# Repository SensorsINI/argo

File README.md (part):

# Argo Autonomous Sailboat

An autonomous sailboat system based on Dragonforce 65 hull, running on Orange Pi Zero 2W with ROS2. The system includes comprehensive sensor integration, autonomous navigation, and safety monitoring.

[argo freecad 3d.webm](https://github.com/user-attachments/assets/29d93eb4-6dfb-44b6-a583-b5699d12e7a1)

## News
- **May 2026:** After ignominious series of problems at CCNW with cabling, water leaks, GPS and many other issues and only 30m of actual seawater sailing, came back to INI to fix these problems. Now IMU is working, GPS is working, dashboard has map display, there are new cable glands and a new hull that has been air-pressure tested for leaks. We are ready now for water trials again.
- **Mar 2026:** Version 4 of argo PCB with bug fixes, wind sensor on separate I2C bus, and new buzzer. Version 3 of the wind sensor PCB with RGBW LED controller. See [Argo2: Robot Sailboat](https://docs.google.com/presentation/d/15X9GgjOmHowyNMNPRnduzyOgwyVcawP_Lhy54-Hc9cc/edit?usp=sharing) slides presented online at [Embodied Intelligence Conference](https://ei26.embodied-intelligence.org/) 20 March 2026.
- **Feb 2026:** Updated [wind sensor design PCB and housing](pcb/WindSensor/WindSensor-rev1/) complete. 3D parts for wind sensor I2C cable and mast step up completed and printed.
- **Jan 2026:** [Argo main PCB version 3](pcb/argo-v9-stable/argo-v9-stable-rev3/) completed and seems fully functional with no surgery needed.
- **Aug-Dec 2025:** Intense development of new [Argo PCB](pcb/) and [ROS2 software framework](nodes/). System services developed (see [`power_control/argo_power_control.py`](power_control/argo_power_control.py) and [`launch/argo_lifecycle_manager.py`](launch/argo_lifecycle_manager.py)) along with robust [lifecycle management](launch/argo_lifecycle_manager.py) and [battery/power control](power_control/argo_power_control.py).
- **Oct-Nov 2025:** Developed first version of [Argo simulator](simulator/).  
  - See [simulator/sailboat-playground/README.md](simulator/sailboat-playground/README.md) for usage and architecture.  
  - Additional docs: [Simulation Guide](docs/SIMULATION.md), [Debug Simulation Guide](docs/README-debug-simulation.md)  

## Installation

Pick **Argo (boat)** or **Host (PC)** below. ROS 2 **must match your Ubuntu LTS**: 22.04 (Jammy) → **Humble**; 24.04 (Noble) → **Jazzy**. Use the official [ROS 2 Ubuntu (deb) install](https://docs.ros.org/en/jazzy/Installation/Ubuntu-Install-Debs.html) page that corresponds to your ROS release.

### Argo (boat — Orange Pi Zero 2W)

On the robot, the stack targets **Ubuntu 22.04–based** Armbian and **ROS 2 Humble**. Bring up I²C/UART/PWM overlays, the radio/servo kernel module, Python dependencies, systemd services, and power control as described in the [launch](launch/) tree.

```bash
cd ~/argo   # or your clone path
sudo apt update && sudo apt upgrade -y
# Install ROS 2 Humble (.deb), then in each shell you use for builds:
#   source /opt/ros/humble/setup.bash

make install-all          # Python deps + optional hardware (see Makefile / messages)
make install-argo-cli
source ~/.bashrc
make -C launch install    # install systemd units; enable per docs
```

#### First-time SD card and hardware bring-up

**1. Flash Orange Pi OS** using Orange Pi Imager or equivalent.

**2. Initial system setup**

```bash
sudo apt update && sudo apt upgrade -y
sudo apt install python3-pip python3-dev build-essential
sudo apt install i2c-tools device-tree-compiler git
sudo apt install ros-humble-desktop
```

**3. Clone repository**

```bash
cd /home/orangepi
git clone https://github.com/SensorsINI/argo.git
cd argo
```

**4. Python and ROS helpers**

```bash
make install-python-deps   # requirements.txt on the boat
# If needed:
sudo apt install python3-rclpy python3-std-msgs python3-geometry-msgs
```

**5. Hardware configuration**

Edit `/boot/orangepiEnv.txt` and add overlays:

```
overlays=pi-i2c0 disable-uart0 ph-uart5 pi-pwm2 pi-pwm4
user_overlays=argo_radio_servo_overlay
```

Build and load the PWM capture module:

```bash
cd ~/argo/nodes/pwm_capture_module
make all
sudo modprobe argo_radio_servo_module   # or reboot
```

Add your user to hardware groups:

```bash
sudo usermod -a -G i2c,dialout $USER
# log out and back in
```

**6. Verify**

```bash
sudo i2cdetect -y 0
lsmod | grep argo
ls -la /sys/kernel/argo_radio_servo/
sudo cat /dev/ttyS5
```

**7. CLI and services**

```bash
make install-argo-cli && source ~/.bashrc
make -C launch install
sudo systemctl daemon-reload
sudo systemctl enable argo_launch.service
```

### Host (simulation, Foxglove, remote monitoring)

Use this on a **laptop or workstation** for **local simulation** (`asim`), **Foxglove Studio** (same Wi‑Fi, VPN, or SSH tunnel), log playback, and shore-side scripts. The boat still runs ROS 2 on the Orange Pi; your host subscribes/records like any ROS 2 client. **LoRa** is a boat link—the monitoring machine uses normal network ROS 2 or recorded bags unless you run a separate LoRa gateway stack.

**Prerequisites:** Ubuntu **22.04** or **24.04** (see mapping to Humble/Jazzy above), `git`, `make`, `sudo`, and network access for `apt`.

**One-shot bootstrap (Ubuntu 22.04 or 24.04):**

```bash
cd /path/to/argo
make host-setup
source ~/.bashrc                     # reload Argo dotfiles in this terminal (or open a new tab)
# Dotfiles auto-source the first ROS found under /opt/ros (jazzy, iron, humble, rolling) when ROS_DISTRO is unset.

source .venv/bin/activate            # optional; pip tooling (argcomplete, pyglet, …)
asim
```

If a command in **this** terminal cannot find `rclpy` or `ros2` right after `host-setup`, the ROS underlay is not loaded yet: run `source ~/.bashrc` (as above), or explicitly `source /opt/ros/humble/setup.bash` / `source /opt/ros/jazzy/setup.bash` matching your install.

`make host-setup` **refuses to run on Orange Pi** (use `make install-all` on the boat). It:

- Adds **`/etc/apt/sources.list.d/ros2-latest.list`** only if no file already references **packages.ros.org/ros2/ubuntu** (avoids a second `Signed-By` if you installed ROS 2 from the official doc first)  
- Installs **`ros-<distro>-ros-base`** when `/opt/ros/<distro>` is absent (Jammy → `humble`, Noble → `jazzy`, or override with `ROS_DISTRO=`)  
- Runs **`make install-deps`** (single `apt-get update`, then Argo’s ROS .deb set, Foxglove bridge, MCAP storage)  
- Runs **`make setup-venv`** (creates `.venv` with **uv** if available, otherwise `python3 -m venv`, and installs **`requirements-host.txt`**) then **`make install-python-deps`** (same host requirements file again into `.venv`—idempotent on a PC)  
- Runs **`make install-argo-cli`** and **`make submodule-init`** (`install-argo-cli` appends **`source <repo>/dotfiles/bashrc`** to **`~/.bashrc`**; that file auto-sources **`/opt/ros/<distro>/setup.bash`** when **`ROS_DISTRO`** is not already set)  

**Tab completion (optional):** Global argcomplete is **not** installed automatically on every shell (keeps login fast). After `host-setup`, run once: `activate-global-python-argcomplete3 --user` or `activate-global-python-argcomplete --user`, or see [dotfiles/README.md — Tab Completion Setup](dotfiles/README.md#tab-completion-setup).

Force a distro explicitly, e.g. on non-LTS or mixed images:

```bash
make host-setup ROS_DISTRO=jazzy
```

If **`apt-get update`** reports **conflicting Signed-By** for `packages.ros.org/ros2/ubuntu`, you have two ROS 2 source files—keep one. For example, if you already used the official installer, remove Argo’s duplicate and refresh: `sudo rm -f /etc/apt/sources.list.d/ros2-latest.list && sudo apt-get update`.

`install-ros2-apt-repo` checks for an existing ROS 2 source with **`sudo grep`** because some `sources.list.d` entries are **root-only**; without that, Make could miss your working repo and add a second file.

**Foxglove:** with ROS sourced on the machine that runs the bridge, start `ros2 run foxglove_bridge foxglove_bridge` and connect from [Foxglove Studio](https://foxglove.dev/) to `ws://<that-host-ip>:8765`.

### Makefile targets and shell aliases (reference)

- `make host-setup` — **host-only** full bootstrap (see above)  
- `make install-deps` — ROS packages for the current `ROS_DISTRO` (Foxglove, MCAP, …)  
- `make install-python-deps` — robot uses `requirements.txt`; host uses `requirements-host.txt` (prefers `.venv` if present)  
- `make install-hardware` — PWM module (boat)  
- `make install-all` — boat-oriented dependency + hardware path  
- `make -C launch …` — lifecycle systemd helpers  

After `make install-argo-cli`, common aliases include `al` / `aq` / `ars` (services), `as` / `asq` (status), `asim` (local sim), `ar` / `ac` (recording), `alog`, `ah`. Run `make help` and see [dotfiles/](dotfiles/).

## System Overview

The Argo system consists of multiple ROS2 nodes that work together to provide autonomous sailing capabilities:

- **Sensor Nodes**: GPS (u-blox NEO-M9N), IMU ([Adafruit BNO085](https://www.adafruit.com/product/4754)), Wind sensors (3x Sensirion SDP3x), Battery/Water monitoring
- **Control Interface**: PWM capture for radio control and servo output  
- **Autonomous Control**: Navigation and sail trimming algorithms
- **Safety Systems**: Manual override, battery monitoring, water intrusion detection

### Demo Video
See the Argo autonomous sailboat in action at the 2024 CCNW (before current waterproofing and PCB developements): [Argo Sailboat Demo](https://youtu.be/tjC1262BsCY?si=1GFPk1QcOqpzw8h2)

## Hardware Platform
The main PCB design for Argo is available in the [pcb/](pcb/) folder. The latest board version is [rev4](pcb/argo-v9-stable/argo-v9-stable-rev4/), which contains the current sailboat control and sensor interface design.

- **Orange Pi Zero 2W** (Allwinner H618 SoC)
- **GPS**: u-blox NEO-M9N via UART5 (/dev/ttyS5)
- **IMU**: [Adafruit BNO085](https://www.adafruit.com/product/4754) 9-DOF Orientation IMU via I2C0 (0x4a)
- **Wind Sensor**: 3x Sensirion SDP3x differential pressure sensors via I2C0 (0x21, 0x22, 0x23). This PCB includes an RGBW LED and its I2C controller PCA9632 at individual address 0x62 (0x70 is LED All Call).  
  - **Design files:** See [`pcb/WindSensor/WindSensor-rev1/`](pcb/WindSensor/WindSensor-rev1/) directory for full hardware schematics, layout, and BOM.
- **ADC**: MAX11612 for battery/water sensing via I2C0 (0x34)
- **Environment**: SHT45 temperature/humidity via I2C0 (0x44)
- **PWM I/O**: Custom kernel module for radio control and servo interfaces with high impedance safety mode
- **LORA**: Long range radio based on RA-01 radio module from ai-thinker.com using SX1276 LORA chip

### Hardware Replacement and MAC Address Cloning

The Argo system is designed to handle frequent SBC hardware replacements (due to damage) while maintaining network identity. The WiFi MAC address is frozen to a consistent value (`c8:26:e2:6c:58:ba`) stored in `network/ARGO_MAC_ID.txt` and committed to git. This ensures:

- **Network Stability**: Same MAC address across hardware changes maintains network access (uzh-iot, ZeroTier, tobi-wlan)
- **SD Card Portability**: Same SD card works seamlessly with different SBC hardware
- **Automatic Configuration**: Run `make freeze-mac-address` after hardware replacement to restore network identity

See [Network Improvements Documentation](network/README.md#mac-address-cloning-hardware-replacement) for details.

### Servo Control Hardware

The Argo system uses a shared control circuit design that allows both radio control and autonomous software control of servos through a fail-safe high impedance switching mechanism:

#### Stock DF65 V6 (2018) Servo Configuration
- **Sail Winch Servo**: Joysway #880545
  - Type: Standard sail winch servo with high-precision plastic gears
  - Operating voltage: 4.8V to 6.0V
  - PWM frequency: 1520μs/50Hz
  - **Input impedance: 12kΩ** (measured)
  - **Circuit resistor: 3.3kΩ** (optimized for proper signal level)

- **Rudder Servo**: Joysway #881504  
  - Type: Digital metal gear servo
  - Operating voltage: 4.8V to 6.0V
  - PWM frequency: 1520μs/330Hz
  - **Input impedance: 400kΩ** (measured)
  - **Circuit resistor: 10kΩ** (standard value works well)

#### Shared Control Circuit Design
The hardware implements a fail-safe shared control circuit where:

1. **High Impedance Safety Mode**: When PWM outputs are disabled (high impedance), radio control signals pass through resistors directly to servo inputs
2. **Software Control Mode**: When PWM outputs are enabled, software generates servo control signals
3. **Voltage Divider Considerations**: Resistor values are optimized based on servo input impedance:
   - Sail servo: 3.3V × (12kΩ / (3.3kΩ + 12kΩ)) = 2.6V (adequate signal level)
   - Rudder servo: 3.3V × (400kΩ / (10kΩ + 400kΩ)) = 3.2V (excellent signal level)

#### GPIO Pin Assignments (Orange Pi Zero 2W)
- **PI11 (Pin 7)**: Radio Rudder Input - GPIO input with interrupt capability
- **PI13 (Pin 26)**: Radio Sail Input - GPIO input with interrupt capability  
- **PI12 (Pin 33)**: Servo Rudder Output - PWM2 channel, high impedance when disabled
- **PI14 (Pin 16)**: Servo Sail Output - PWM4 channel, high impedance when disabled

This design ensures **radio control always works** when software is not running, providing maximum safety for autonomous sailboat operation.

## ROS2 Software Architecture
```mermaid
flowchart TB
  subgraph OUTPUTS[Output Nodes]
    RSR[rudder_sail_radio primary actuation output]
    LORA[lora long range communications]
  end

  CTRL[controller primary decision and control logic]

  subgraph SAFETY[Critical Safety Services]
    BW[battery_water critical]
    LA[launch critical]
  end

  subgraph SENSORS[Sensor Input Layer]
    GPS[gps]
    IMU[imu BNO085]
    ANEM[anem]
  end

  VR[Visualization and Recording]

  GPS --> CTRL
  IMU --> CTRL
  ANEM --> CTRL
  CTRL --> RSR

  BW --> LA
  LA --> CTRL

  CTRL --> VR

  CTRL -.-> LORA
```

### Project Organization

The Argo system follows a modular ROS2 architecture with clear separation of concerns:

**Directory Structure:**
- **`nodes/`** - Individual ROS2 nodes (Python-based sensor interfaces)
- **`launch/`** - Lifecycle management, systemd services, and launch configurations
- **`power_control/`** - Power management system (separate ROS2 package)
- **`foxglove/`** - Visualization layouts for Foxglove Studio
- **`simulator/`** - Sailboat simulation submodule (sailboat-playground)

## Other READMEs

### Core System Documentation
- [**Systemd Services Architecture**](docs/README-services.md) - Service dependencies, boot sequence, and troubleshooting
- [**Network Improvements**](network/README.md) - WiFi reconnection, MAC address cloning, and NetworkManager configuration
- [**ZeroTier VPN Setup**](docs/README_zerotier.md) - ZeroTier VPN configuration, SSH access, and network management
- [**Power Control System**](power_control/README.md) - Power button, LED control, and graceful shutdown
- [**Systemd Integration**](launch/README.md) - Launch system and lifecycle management
- [**Shutdown Fixes**](docs/SHUTDOWN_FIXES.md) - Shutdown procedure fixes and improvements
- [**LED Status Guide**](docs/ARGO_LED_STATUS_GUIDE.md) - LED status display and hatch cover indicators

### Development & Simulation
- [**Simulation System Overview**](simulator/README.md) - Sailboat simulation framework
- [**Simulation Documentation**](docs/SIMULATION.md) - Simulation setup and usage
- [**Debug Simulation**](docs/README-debug-simulation.md) - Debugging simulation issues

### Hardware & Configuration
- [**I2C Configuration**](docs/README-i2c.md) - I2C bus setup and troubleshooting
- [**LoRa (onboard ↔ shore)**](docs/README-lora-to-shore.md) - SX1276 / Waveshare hardware, link parameters, packet header
- [**IMU BNO085**](docs/README-imu-bno085.md) - C++ driver, Python bridge, calibration, `argo_bno085` service
- [**Thermal monitoring (SBC)**](docs/README-thermal-monitoring.md) - Orange Pi GPU/CPU/DDR temperature logging (`argo_thermal_monitor`)
- [**Watchdog Configuration**](docs/README-watchdog.md) - Watchdog setup for Orange Pi Zero 2W
- [**CPU Frequency Tuning**](docs/README-cpufreq-tuning-service.md) - CPU governor configuration
- [**Battery & Power Monitoring**](docs/README-battery-power.md) - Battery monitoring system
- [**Battery Panel Setup**](docs/BATTERY_PANEL_SETUP.md) - Battery panel configuration
- [**SD Card Backup**](docs/README-sd-card-backup.md) - SD card backup procedures
- [**DVFS Userspace Access**](docs/dvfs_userspace_access.md) - Dynamic voltage and frequency scaling

### Visualization & Analysis
- [**Foxglove Visualization**](foxglove/README.md) - Real-time visualization setup
- [**Foxglove Debugging**](docs/FOXGLOVE_DEBUGGING.md) - Debugging Foxglove issues
- [**Foxglove Joystick Setup**](docs/FOXGLOVE_JOYSTICK_SETUP.md) - Joystick control configuration
- [**3D Visualization**](docs/README-3d-visualization.md) - 3D visualization configuration
- [**Visualization Marker Persistence**](docs/VISUALIZATION_MARKER_PERSISTENCE.md) - Marker persistence in visualization
- [**Adding Sailing Maps**](docs/README-adding-sailing-maps.md) - Map integration guide
- [**Maps Documentation**](maps/README-maps.md) - Sailing area maps

### Remote Access & Interface
- [**Remote Desktop VNC**](docs/README_REMOTE_DESKTOP_VNC.md) - VNC remote desktop setup
- [**Web Dashboard**](docs/WEB_DASHBOARD_README.md) - Mobile-friendly web interface

### CLI & User Interface
- [**CLI Completion**](docs/CLI_COMPLETION.md) - Command-line completion setup
- [**Completion Quickstart**](docs/COMPLETION_QUICKSTART.md) - Quick start guide for CLI completion
- [**MOTD Customization**](docs/MOTD_CUSTOMIZATION.md) - Message of the day customization

### Additional Resources
- [**ROS2 Nodes**](nodes/README.md) - Node documentation and configuration
- [**Scripts**](scripts/README.md) - Utility scripts documentation
- [**Dotfiles Setup**](dotfiles/README.md) - CLI aliases and shell configuration
- [**Persistent Logging**](docs/README-persistent-logging.md) - Logging configuration

### Simulation Support

Argo includes comprehensive simulation support for development and testing:

**Local Simulation:**
- Runs simulator directly on Orange Pi
- Uses sailboat-playground or mock simulator
- Excludes conflicting hardware nodes (GPS, IMU, anemometer, radio control)
- Perfect for algorithm development and testing

**Remote Simulation:**
- Offloads CPU-intensive simulation to remote machine
- SSH tunnel for ROS2 communication
- Centralized configuration management
- Ideal for resource-constrained environments

**Quick Start:**
```bash
# Local simulation
python3 launch/argo_lifecycle_manager.py simulate_local

# Remote simulation (requires setup)
python3 launch/argo_lifecycle_manager.py simulate_remote

# Or use helper scripts (equivalent flow):
./scripts/remote_simulator_tunnel.sh &
python3 scripts/remote_simulator_launch.py &
./scripts/launch_simulator_remote.sh
```

## Directory Overview

### `launch/` - System Management & Services
Central control hub for the entire Argo system:
- **`argo_lifecycle_manager.py`** - Core lifecycle management with intelligent monitoring
- **`argo_*.sh`** - Shell scripts for start/stop/restart/status operations
- **`argo-launch.service`** - Systemd service configuration
- **`argo_gui.py`** - GTK-based status monitoring GUI
- **`argo_storage_monitor.py`** - Storage space monitoring and notifications
- **`Makefile`** - Service installation and management automation

### `nodes/` - ROS2 Node Implementations
Hardware interface and control nodes:
- **Sensor Nodes**: `gps.py`, `bno085.py`, `anem.py`, `argo_battery_water.py`, `temp_monitor.py`
- **Control Nodes**: `rudder_sail_radio.py`, `controller.py`, `record.py`
- **`pwm_capture_module/`** - Custom kernel module for radio control and servo interfaces
- **Configuration files**: `argo.yaml`, calibration data, and support utilities

### `power_control/` - Hardware Power Management
Standalone ROS2 package for power button and LED control:
- **`argo_power_control.py`** - Main power control node with GPIO management
- **Hardware Functions**: Power button monitoring, LED patterns (heartbeat/SOS), graceful shutdown
- **ROS2 Services**: LED control, system health monitoring
- **`Makefile`** - Independent installation and service management

### `pcb/` - Hardware Design Files
Custom PCB development for production-ready integration:
- **`argo-v9-stable/`** - Current stable PCB design (KiCad project files)
- **`datasheets/`** - Component specifications and reference materials
- **`orange-pi/`** - Orange Pi Zero 2W integration documentation and pin definitions
- **Bill of Materials**: Component sourcing and assembly documentation

### `foxglove/` - Real-time Visualization
Foxglove Studio integration for live system monitoring:
- **`argo_ros2.json`** - Pre-configured dashboard layout for Argo sailboat
- **`custom-argo-panel/`** - TypeScript custom panel for specialized boat visualization
- **`setup_foxglove.sh`** - Automated Foxglove Bridge configuration and startup

### `system-monitoring/` - Optional System Monitoring Services
Optional system-level monitoring services for debugging and development:
- **`Makefile`** - Installation and management of system monitoring services
- **`services/`** - Systemd service files for system monitoring
- **`scripts/`** - Monitoring scripts for boot history, memory, processes, etc.
- **Not installed by default** - Use `make install-system-monitoring` to install

**Core ROS2 Nodes:**
- **`gps.py`** - GPS receiver interface (UART5, u-blox NEO-M9N)
- **`bno085.py`** - 9-DOF Orientation IMU with sensor fusion (I2C, [Adafruit BNO085](https://www.adafruit.com/product/4754))
- **`anem.py`** - Wind sensor array (3x SDP3x pressure sensors)
- **`argo_battery_water.py`** - Power monitoring and safety systems
- **`rudder_sail_radio.py`** - Radio control input and servo output interface
- **`controller.py`** - Autonomous navigation and sail control algorithms
- **`record.py`** - Data recording management (ROS2 bag files)
- **`temp_monitor.py`** - System temperature monitoring
- **`argo_unified_simulator_bridge.py`** - Unified simulator bridge for local and remote simulation

### Node Lifecycle Management

The Argo system uses a sophisticated lifecycle management approach centered around **`argo_lifecycle_manager.py`**:

**Key Features:**
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
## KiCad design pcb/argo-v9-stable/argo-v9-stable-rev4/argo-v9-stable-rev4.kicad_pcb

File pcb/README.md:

# PCB Design Files

This directory contains all the printed circuit board (PCB) design files, libraries, and documentation for the Argo autonomous sailboat project.

The design was done with KiCad version 9 stable.  
**It is important to use the stable KiCad version, not the development release, since KiCad will not open files from later versions!**  
- [Download KiCad stable here](https://www.kicad.org/download/)

## See also
Updated wind sensor design in [WindSensor](WindSensor).
## Current PCB
The current stable PCB [Argo PCB rev4](argo-v9-stable/argo-v9-stable-rev4) that will be tested at CapoCaccia 2026 is shown below, plugged into the OrangePiZero 2W. The only missing board is the GPS module, which sits on the standoffs. Note how the Ra-01 LORA module is soldered directly to the PCB to lower it to fit under the rudder winch. The white JST headers connect to water sensor, hatch power button with RGB LED, and 2S LiPo battery charger/balance cable. The large cables connect power from the LiPo battery, which sits alongside the keel/mast hull insert. The two black headers connect to the IMU on the rudder/winch servo chassis, and the wind sensor at the top of the mast. The board has a big white dual-coil power relay that completely cuts power when the boat is powered off.  The upper small black chip at lower left are the ADC that converts battery voltage, sail winch and rudder current, and water sensor voltage. The smaller chip below this is the humidity and PCB temperature sensor. The 4 large SMD caps at top left, below the inductor, are just to the left of the LiPo battery charger chip. The USB power input for charging is at lower right; it connects to the waterproof hatch USB port with a flex cable. Note how all cables exit on right because fore is the only available direction for connections; the PCB sits nestled up against the rudder insert and partly below the rudder/winch tray.

Outstanding bugs: The rev4 PCB requires soldering a single 10k resistor to ground from the buzzer testpoint to prevent buzzer activation during boot. This resistor should be added to rev 5.

## Directory Structure

### `argo-v9-stable/`
The main PCB design files for the Argo v9 stable revision:
- **Schematic and PCB files**: KiCad project files for the main control board
- **3d-models/**: 3D model files for mechanical integration
- **Argo footprint Library.pretty/**: Custom KiCad footprint library with hand-solderable components
- **argo-v9-stable-rev4/**: Current production (rev4) manufacturing files (almopst fully functional, no modifications required except 10k pulldown on BUZZER and direct LORA soldering to PCB)
- **bom/**: Bill of Materials (BOM) files including interactive HTML BOM

### `orange-pi/`
Orange Pi Zero 2W integration files:
- **orange_pi_zero_2w.kicad_sym**: KiCad symbol for Orange Pi Zero 2W
- **orange_pi_zero_2w_pins.lib**: Pin definition library
- **3d/**: 3D models for Orange Pi Zero 2W
- **H616_Datasheet_V1.0_cleaned.pdf**: Allwinner H616 SoC datasheet
- **OPi_ZERO_2W_SCH.pdf**: Orange Pi Zero 2W schematic
- **OPi_ZERO_2W_V1_1_1A pcb layout.pdf**: PCB layout reference

## Key Components

### Main Control Board (Argo v9)
- **Microcontroller**: Orange Pi Zero 2W (Allwinner H618)
- **Power Management**: USB-C PD controller (AP33771C), power switching
- **Sensors**: 
  - GPS: u-blox NEO-M9N
  - IMU: Sparkfun BNO085
  - Wind: 3x Sensirion SDP3x differential pressure; see WindSensor folder
  - Environment: SHT45 temperature/humidity
  - Battery/Water: MAX11612 ADC
- **Interfaces**: I2C, UART, PWM capture/output, USB-C

### Design Philosophy
- **Hand-solderable components**: All footprints designed for manual assembly
- **Robust power management**: Dual coil relay, USB LiPo charging.
- **Robust I2C**: The wind sensor using different I2C bus than internal components, in case bus is shorted by water.

### Assembly Notes
- All components are hand-solderable. SMD pads have been made extra long to allow heat application and for excess solder.

## Development Tools

### KiCad Version
- **Required**: KiCad 9.0 or later
- **Footprint Library**: Custom "Argo footprint Library" with hand-solderable components

### 3D Models
- **Mechanical Integration**: 3D models have been built for all PCB components for enclosure design
- **Assembly Verification**: Use FreeCAD 1.1+ for clearance checking.

## Documentation

### Testing and Validation
- **In-Circuit Testing**: Test points provided for key signals

## Related documentation

- **[Main project README](../README.md)** — Overall system documentation
- **[Software nodes](../nodes/README.md)** — ROS2 nodes on the Orange Pi
- **[Launch](../launch/README.md)** — Startup scripts and lifecycle management
- **[Power control](../power_control/README.md)** — Battery, button, shutdown, and services; **[detailed reference](../power_control/ARGO_POWER_CONTROL_README.md)** — GPIO, hooks, and service behavior
- **[Wind sensor PCB](WindSensor/README.md)** — SDP3x wind sensor board design
- **[Orange Pi KiCad](orange-pi/README.md)** — KiCad symbol, footprint, and 3D models for the OPI header
- **[PCB v4 → v5 migration](../docs/README-argo-pcb-v4-v5-migration.md)** — Planned pin and bus changes for the next revision
- **[I2C buses](../docs/README-i2c.md)** — I2C configuration and recovery on the board
- **[Pin and bus reference](../docs/README-pins-i2c.md)** — Orange Pi 40-pin header: power, I2C, SPI, UART, PWM

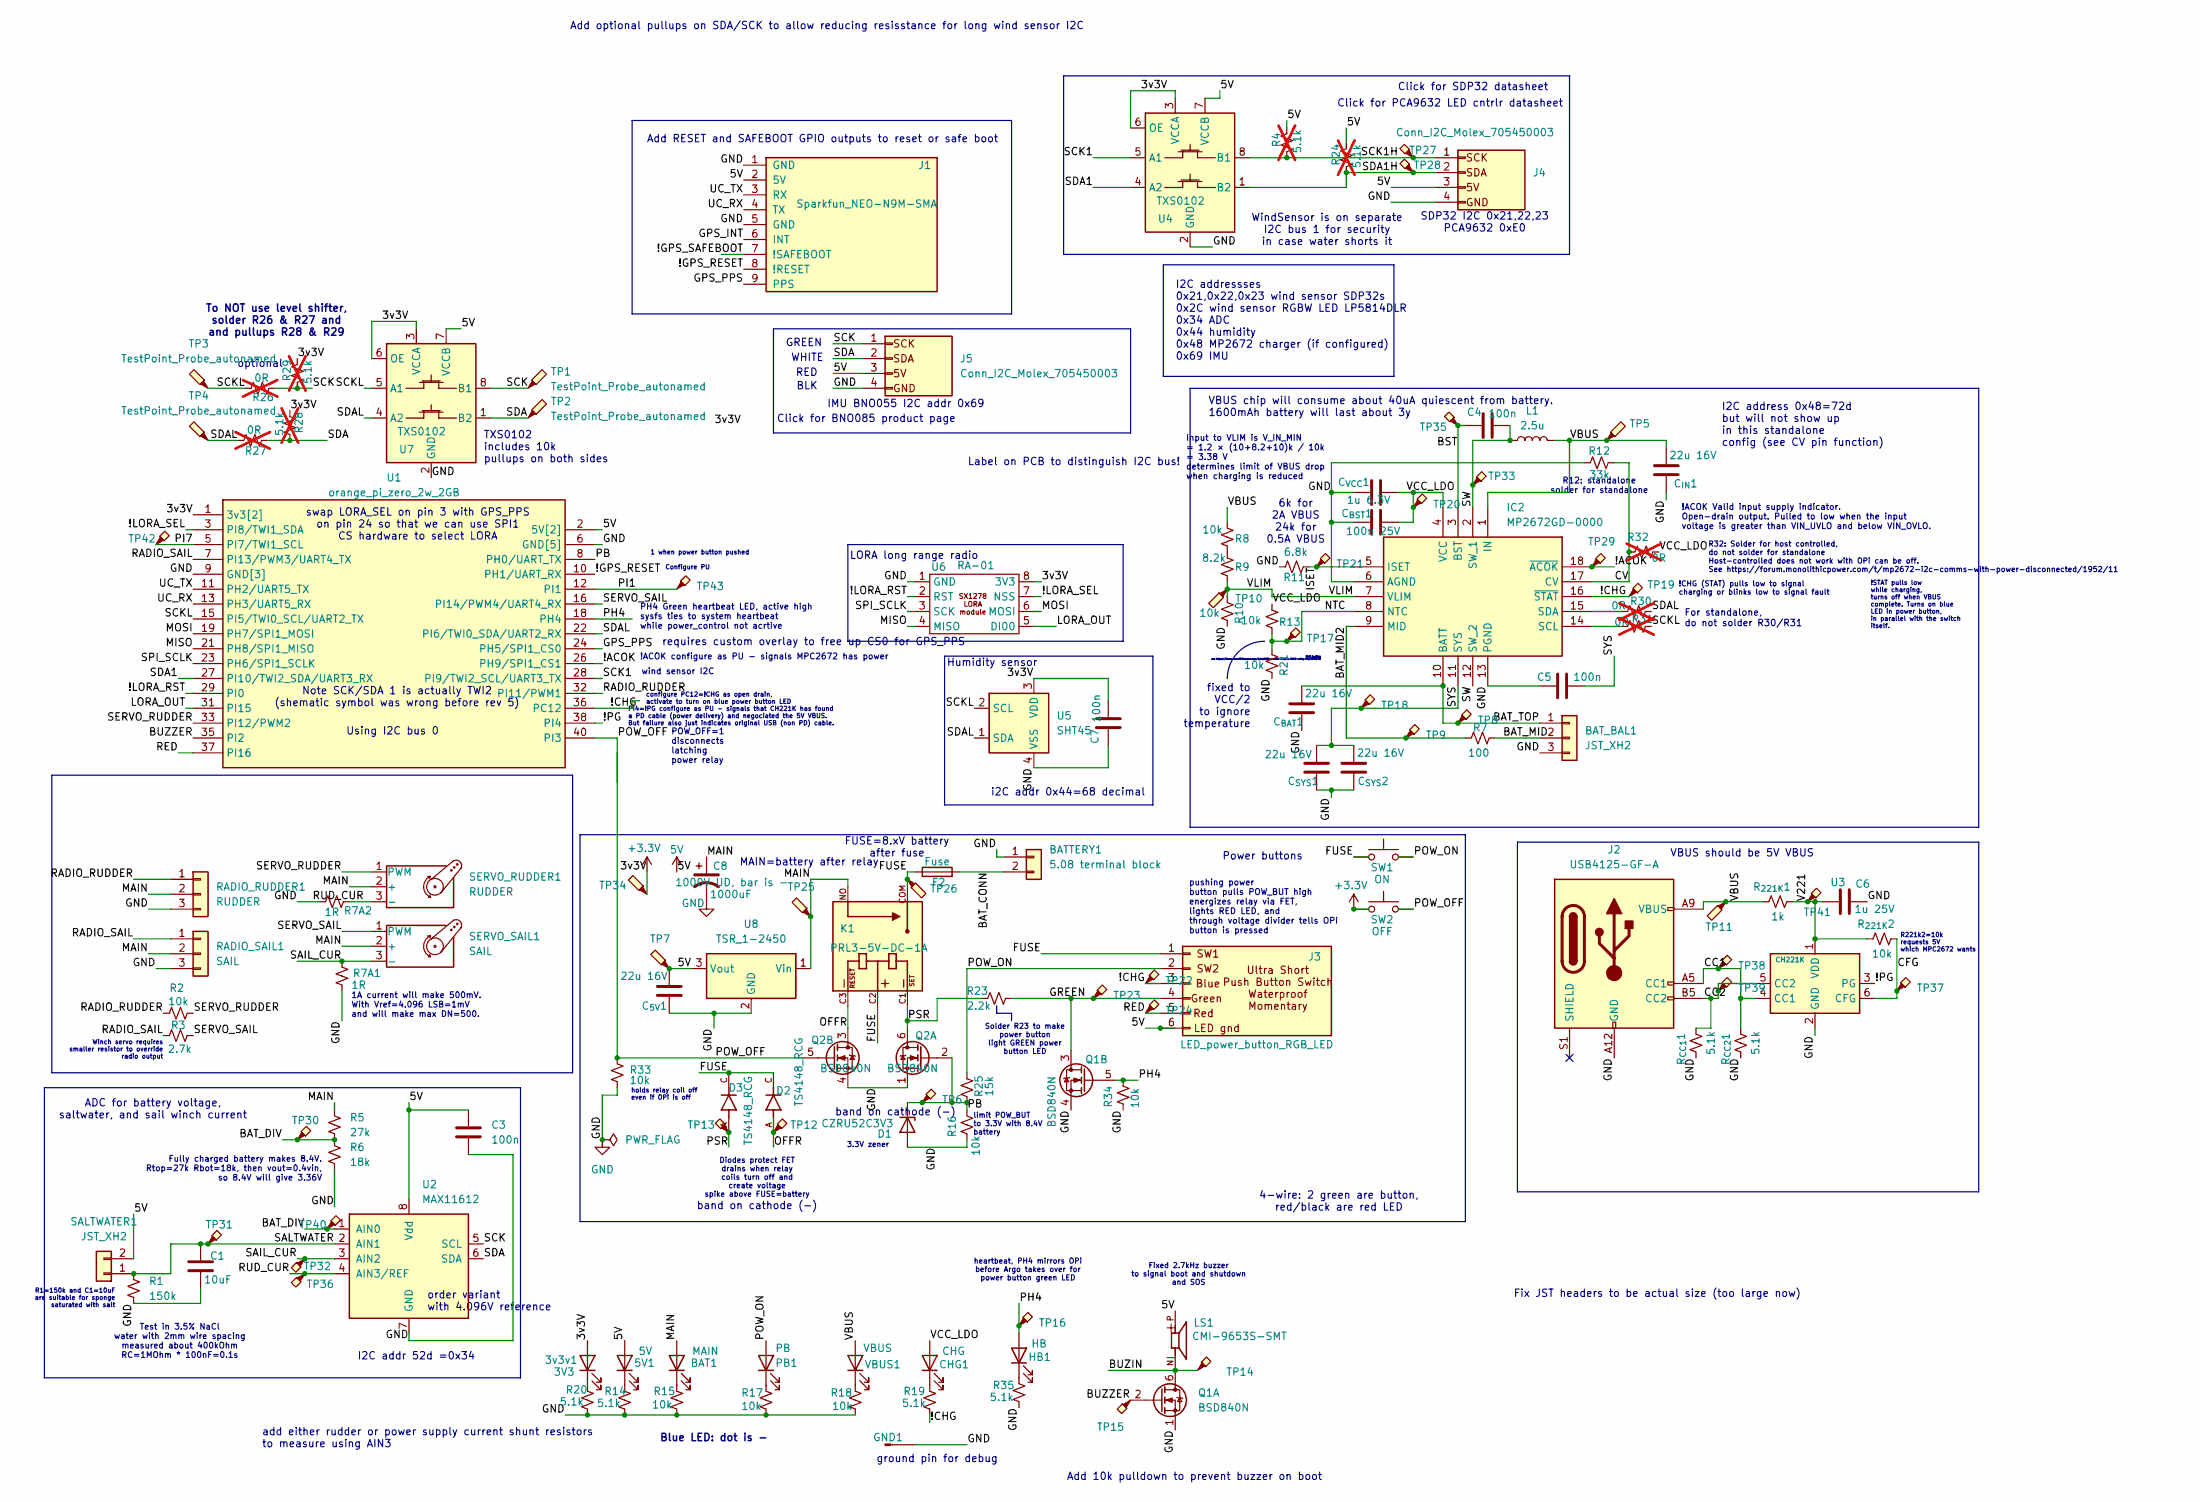
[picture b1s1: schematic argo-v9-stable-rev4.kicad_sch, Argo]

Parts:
3v3v1: 3V3; LED_0603_1608Metric_Pad1.05x0.95mm_HandSolder
5V1: 5V; LED_0603_1608Metric_Pad1.05x0.95mm_HandSolder
BAT1: MAIN; LED_0603_1608Metric_Pad1.05x0.95mm_HandSolder
BATTERY1: 5.08 terminal block; TerminalBlock_Phoenix_MKDS-1,5-2-5.08_1x02_P5.08mm_Horizont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
BAT_BAL1: JST_XH2; JST_XH_S3B-XH-A-1_1x03_P2.50mm_Horizontal
C1: 10uF; C_0603_1608Metric_Pad1.08x0.95mm_HandSolder
C3, C4, C5, C7: 100n; C_0603_1608Metric_Pad1.08x0.95mm_HandSolder
C6: 1u 25V; C_0603_1608Metric_Pad1.08x0.95mm_HandSolder
C8: 1000uF; PCAP_10x10-ELECT_NCA; digikey have 4 in lab
CHG1: CHG; LED_0603_1608Metric_Pad1.05x0.95mm_HandSolder
C_{5V}1: 22u 16V; C_1210_3225Metric_Pad1.33x2.70mm_HandSolder
C_{BAT}1: 22u 16V; C_1210_3225Metric_Pad1.33x2.70mm_HandSolder
C_{BST}1: 100n 25V; C_0603_1608Metric_Pad1.08x0.95mm_HandSolder
C_{IN}1: 22u 16V; C_1210_3225Metric_Pad1.33x2.70mm_HandSolder
C_{SYS}1, C_{SYS}2: 22u 16V; C_1210_3225Metric_Pad1.33x2.70mm_HandSolder
C_{VCC}1: 1u 6.3V; C_0603_1608Metric_Pad1.08x0.95mm_HandSolder
D1: CZRU52C3V3; D_0603_1608Metric_hand_solder
D2, D3: TS4148_RCG; DIO_TS4148_RCG; PARTREV A2301
F2: Fuse; Fuse_Smd- Nano SMF AliExp
GND1: Conn_01x01_Pin; Pin_D1.0mm_L10.0mm_LooseFit
HB1: HB; LED_0603_1608Metric_Pad1.05x0.95mm_HandSolder
IC2: MP2672GD-0000; QFN40P200X300X100-18N-D-handsolder; Manufacturer_Part_Number MP2672GD-0000
J1: Sparkfun_NEO-N9M-SMA; Sparkfun_NEO-M9N-SMA
J2: USB4125-GF-A; USB_C_Receptacle_GCT_USB4125-xx-x-0190_6P_TopMnt_Horizontal
J3: LED_power_button_RGB_LED; JST_XH_S6B-XH-A_1x06_P2.50mm_Horizontal
J4, J5: Conn_I2C_Molex_705450003; I2C_header
K1: PRL3-5V-DC-1A; RELAY_PRL3-5V-DC-1A; PARTREV 1.0
L1: 2.5u; L_Aliexpress_2.5uH
LS1: CMI-9653S-SMT; CUI_CMI-9653S-SMT
PB1: PB; LED_0603_1608Metric_Pad1.05x0.95mm_HandSolder
Q1, Q2: BSD840N; SOT-363_SC-70-6-handsolder
R1: 150k; R_0603_1608Metric_Pad0.98x0.95mm_HandSolder
R2, R8, R10, R13, R15, R16, R17, R18, R21, R33, R34: 10k; R_0603_1608Metric_Pad0.98x0.95mm_HandSolder
R3: 2.7k; R_0603_1608Metric_Pad0.98x0.95mm_HandSolder
R4, R24, R28, R29: 5.1k; R_0603_1608Metric_Pad0.98x0.95mm_HandSolder; not fitted
R5: 27k; R_0603_1608Metric_Pad0.98x0.95mm_HandSolder
R6: 18k; R_0603_1608Metric_Pad0.98x0.95mm_HandSolder
R7: 100; R_0603_1608Metric_Pad0.98x0.95mm_HandSolder
R7A1, R7A2: 1R; R_0603_1608Metric_Pad0.98x0.95mm_HandSolder
R9: 8.2k; R_0603_1608Metric_Pad0.98x0.95mm_HandSolder
R11: 6.8k; R_0603_1608Metric_Pad0.98x0.95mm_HandSolder
R12: 33k; R_0603_1608Metric_Pad0.98x0.95mm_HandSolder
R14, R19, R20, R35: 5.1k; R_0603_1608Metric_Pad0.98x0.95mm_HandSolder
R23: 2.2k; R_0603_1608Metric_Pad0.98x0.95mm_HandSolder
R25: 15k; R_0603_1608Metric_Pad0.98x0.95mm_HandSolder
R26, R27, R30, R31, R32: 0R; R_0603_1608Metric_Pad0.98x0.95mm_HandSolder; not fitted
RADIO_RUDDER1: RUDDER; PinHeader_1x03_P2.54mm_Vertical
RADIO_SAIL1: SAIL; PinHeader_1x03_P2.54mm_Vertical
R_{221K}1: 1k; R_0603_1608Metric_Pad0.98x0.95mm_HandSolder
R_{221K}2: 10k; R_0603_1608Metric_Pad0.98x0.95mm_HandSolder
R_{CC1}1, R_{CC2}1: 5.1k; R_0603_1608Metric_Pad0.98x0.95mm_HandSolder
SALTWATER1: JST_XH2; JST_XH_S2B-XH-A_1x02_P2.50mm_Horizontal
SERVO_RUDDER1: RUDDER; PinHeader_1x03_P2.54mm_Vertical
SERVO_SAIL1: SAIL; PinHeader_1x03_P2.54mm_Vertical
SW1: ON; SW_Tactile_SPST_NO_Straight_CK_PTS636Sx25SMTRLFS
SW2: OFF; SW_Tactile_SPST_NO_Straight_CK_PTS636Sx25SMTRLFS
TP1, TP2, TP3, TP4, TP5, TP7, TP10, TP11, TP25, TP26, TP34: TestPoint_Probe_autonamed; TestPoint_scope_probe_autonamed
TP6, TP8, TP9, TP12, TP13, TP14, TP15, TP16, TP17, TP18, TP19, TP20, TP21, TP22, TP23, TP24, TP27, TP28, TP29, TP30, TP31, TP32, TP33, TP35, TP36, TP37, TP38, TP39, TP40, TP41, TP42, TP43: TestPoint_Probe_autonamed; TestPoint_scope_small_autonamed
U1: orange_pi_zero_2w_2GB; orange_pi_zero_2w
U2: MAX11612; MSOP-8_3x3mm_P0.65mm
U3: CH221K; TSOT-23-6_HandSoldering
U4, U7: TXS0102; SSOP-8_2.95x2.8mm_P0.65mm
U5: SHT45; Sensirion_DFN-4_1.5x1.5mm_P0.8mm_SHT4x_NoCentralPad-handsol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
U6: RA-01; RA-01 SX1278 LORA
U8: TSR_1-2450; Converter_DCDC_TRACO_TSR1-xxxxE_THT
VBUS1: VBUS; LED_0603_1608Metric_Pad1.05x0.95mm_HandSolder

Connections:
5V: 5V1.2 (A), C3.1, C_{5V}1.2, J1.2 (5V), J3.6, J4.3 (5V), J5.3 (5V), LS1.P, R4.2, R24.2, SALTWATER1.2, TP7.1, U1.2 (5V[2]), U1.4 (5V[2]), U2.8 (Vdd), U4.7 (VCCB), U7.7 (VCCB), U8.3 (Vout)
+3.3V: 3v3v1.2 (A), C7.2, R28.2, R29.2, SW2.1, TP34.1, U1.1 (3v3[2]), U1.17 (3v3[2]), U4.3 (VCCA), U4.6 (OE), U5.3 (VDD), U6.8 (3V3), U7.3 (VCCA), U7.6 (OE)
/!ACOK: IC2.18 (~ACOK), TP29.1, U1.26 (PH9/SPI1_CS1)
/!CHG: IC2.16 (~STAT), J3.3, R19.2, TP19.1, TP22.1, U1.36 (PC12)
/!GPS_RESET: J1.8 (!RESET), U1.10 (PH1/UART_RX)
/!GPS_SAFEBOOT: J1.7 (!SAFEBOOT)
/!LORA_RST: U1.29 (PI0), U6.2 (RST)
/!LORA_SEL: U1.3 (PI8/TWI1_SDA), U6.7 (NSS)
/!PG: U1.38 (PI4), U3.3 (PG)
/BAT_CONN: BATTERY1.2, F2.2
/BAT_DIV: R5.2, R6.1, TP30.1, TP40.1, U2.1 (AIN0)
/BAT_MID: BAT_BAL1.2, R7.1
/BAT_MID2: IC2.9 (MID), R7.2, TP9.1
/BAT_TOP: BAT_BAL1.1, C_{BAT}1.2, IC2.10 (BATT), TP8.1
/BST: C4.1, IC2.3 (BST), TP35.1
/BUZIN: LS1.N, Q1.6 (D), TP14.1
/BUZZER: Q1.2 (G), TP15.1, U1.35 (PI2)
/CC1: J2.A5 (CC1), R_{CC2}1.2, TP38.1, U3.4 (CC1)
/CC2: J2.B5 (CC2), R_{CC1}1.2, TP39.1, U3.5 (CC2)
/CFG: R_{221K}2.2, TP37.1, U3.6 (CFG)
/CV: IC2.17 (CV), R12.1, R32.1
/FUSE: D2.C, D3.C, F2.1, J3.1, K1.C2, K1.COM, SW1.1, TP26.1
/GPS_INT: J1.6 (INT)
/GPS_PPS: J1.9 (PPS), U1.24 (PH5/SPI1_CS0)
/GREEN: J3.4, Q1.3 (D), R23.2, TP23.1
/ISET: IC2.5 (ISET), R11.2, TP21.1
/LORA_OUT: U1.31 (PI15), U6.5 (DI00)
/MAIN: BAT1.2 (A), C8.1, K1.NO, R5.1, RADIO_RUDDER1.2, RADIO_SAIL1.2, SERVO_RUDDER1.2 (+), SERVO_SAIL1.2 (+), TP25.1, U8.1 (Vin)
/MISO: U1.21 (PH8/SPI1_MISO), U6.4 (MISO)
/MOSI: U1.19 (PH7/SPI1_MOSI), U6.6 (MOSI)
/NTC: IC2.8 (NTC), R13.2, R21.1, TP17.1
/OFFR: D2.A, K1.C3, Q2.3 (D), TP12.1
/PB: D1.1 (K), Q2.2 (G), R16.2, R25.1, TP6.1, U1.8 (PH0/UART_TX)
/PH4: HB1.2 (A), Q1.5 (G), R34.2, TP16.1, U1.18 (PH4)
/PI1: TP43.1, U1.12 (PI1)
/PI7: TP42.1, U1.5 (PI7/TWI1_SCL)
/POW_OFF: Q2.5 (G), R33.1, SW2.2, U1.40 (PI3)
/POW_ON: J3.2, PB1.2 (A), R25.2, SW1.2
/PSR: D3.A, K1.C1, Q2.6 (D), R23.1, TP13.1
/RADIO_RUDDER: R2.1, RADIO_RUDDER1.1, U1.32 (PI11/PWM1)
/RADIO_SAIL: R3.1, RADIO_SAIL1.1, U1.7 (PI13/PWM3/UART4_TX)
/RED: J3.5, TP24.1, U1.37 (PI16)
/RUD_CUR: R7A2.1, SERVO_RUDDER1.3 (-), TP36.1, U2.4 (AIN3/REF)
/SAIL_CUR: R7A1.1, SERVO_SAIL1.3 (-), TP32.1, U2.3 (AIN2)
/SALTWATER: C1.1, R1.1, SALTWATER1.1, TP31.1, U2.2 (AIN1)
/SCK: J5.1 (SCLK), R26.2, R29.1, TP1.1, U2.5 (SCL), U7.8 (B1)
/SCK1: U1.28 (PI9/TWI1_SCL/UART3_TX), U4.5 (A1)
/SCK1H: J4.1 (SCLK), R4.1, TP27.1, U4.8 (B1)
/SCKL: R26.1, R31.2, TP3.1, U1.15 (PI5/TWI0_SCL/UART2_TX), U5.2 (SCL), U7.5 (A1)
/SDA: J5.2 (SDA), R27.2, R28.1, TP2.1, U2.6 (SDA), U7.1 (B2)
/SDA1: U1.27 (PI10/TWI1_SDA/UART3_RX), U4.4 (A2)
/SDA1H: J4.2 (SDA), R24.1, TP28.1, U4.1 (B2)
/SDAL: R27.1, R30.2, TP4.1, U1.22 (PI6/TWI0_SDA/UART2_RX), U5.1 (SDA), U7.4 (A2)
/SERVO_RUDDER: R2.2, SERVO_RUDDER1.1 (PWM), U1.33 (PI12/PWM2)
/SERVO_SAIL: R3.2, SERVO_SAIL1.1 (PWM), U1.16 (PI14/PWM4/UART4_RX)
/SPI_SCLK: U1.23 (PH6/SPI1_SCLK), U6.3 (SCK)
/SW: C4.2, IC2.2 (SW_1), IC2.12 (SW_2), L1.1, TP33.1
/SYS: C5.2, C_{SYS}1.2, C_{SYS}2.2, IC2.11 (SYS), TP18.1
/UC_RX: J1.4 (TX), U1.13 (PH3/UART5_RX)
/UC_TX: J1.3 (RX), U1.11 (PH2/UART5_TX)
/V221: C6.1, R_{221K}1.2, R_{221K}2.1, TP41.1, U3.1 (VDD)
/VBUS: C_{IN}1.2, IC2.1 (IN), J2.A9 (VBUS), J2.B9 (VBUS), L1.2, R8.1, R_{221K}1.1, TP5.1, TP11.1, VBUS1.2 (A)
/VCC_LDO: CHG1.2 (A), C_{BST}1.2, C_{VCC}1.2, IC2.4 (VCC), R13.1, R32.2, TP20.1
/VLIM: IC2.7 (VLIM), R9.2, R10.1, TP10.1
GND: BATTERY1.1, BAT_BAL1.3, C1.2, C3.2, C5.1, C6.2, C7.1, C8.2, C_{5V}1.1, C_{BAT}1.1, C_{BST}1.1, C_{IN}1.1, C_{SYS}1.1, C_{SYS}2.1, C_{VCC}1.1, D1.2 (A), GND1.1, IC2.6 (AGND), IC2.13 (PGND), J1.1 (GND), J1.5 (GND), J2.A12 (GND), J2.B12 (GND), J4.4 (GND), J5.4 (GND), Q1.1 (S), Q1.4 (S), Q2.1 (S), Q2.4 (S), R1.2, R6.2, R7A1.2, R7A2.2, R10.2, R11.1, R12.2, R14.2, R15.2, R16.1, R17.2, R18.2, R20.2, R21.2, R33.2, R34.1, R35.2, RADIO_RUDDER1.3, RADIO_SAIL1.3, R_{CC1}1.1, R_{CC2}1.1, U1.6 (GND[5]), U1.9 (GND[3]), U1.14 (GND[5]), U1.20 (GND[5]), U1.25 (GND[3]), U1.30 (GND[5]), U1.34 (GND[5]), U1.39 (GND[3]), U2.7 (GND), U3.2 (GND), U4.2 (GND), U5.4 (VSS), U6.1 (GND), U7.2 (GND), U8.2 (GND)
unnamed: 3v3v1.1 (K), R20.1
unnamed: 5V1.1 (K), R14.1
unnamed: BAT1.1 (K), R15.1
unnamed: CHG1.1 (K), R19.1
unnamed: HB1.1 (K), R35.1
unnamed: IC2.14 (SCL), R31.1
unnamed: IC2.15 (SDA), R30.1
unnamed: PB1.1 (K), R17.1
unnamed: R8.2, R9.1
unnamed: R18.1, VBUS1.1 (K)

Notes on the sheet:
optional
Click for SDP32 datasheet
ground pin for debug
Add RESET and SAFEBOOT GPIO outputs to reset or safe boot
requires custom overlay to free up CS0 for GPS_PPS
PI4=!PG configure as PU - signals that CH221K has found a PD cable (power delivery) and negociated the 5V VBUS. But failure also just indicates original USB (non PD) cable.
add either rudder or power supply current shunt resistors to measure using AIN3
FUSE=8.xV battery after fuse
6k for 2A VBUS 24k for 0.5A VBUS
TXS0102 includes 10k pullups on both sides
R221k2=10k requests 5V which MPC2672 wants
wind sensor I2C
To NOT use level shifter, solder R26 & R27 and and pullups R28 & R29
pushing power button pulls POW_BUT high energizes relay via FET, lights RED LED, and through voltage divider tells OPi button is pressed
1A current will make 500mV. With Vref=4.096 LSB=1mV and will make max DN=500.
Input to VLIM is V_IN_MIN = 1.2 × (10+8.2+10)k / 10k = 3.38 V determines limit of VBUS drop when charging is reduced
Note SCK/SDA 1 is actually TWI2 (shematic symbol was wrong before rev 5)
Fully charged battery makes 8.4V. Rtop=27k Rbot=18k, then vout=0.4vin, so 8.4V will give 3.36V
BLK
Solder R23 to make power button light GREEN power button LED
fixed to VCC/2 to ignore temperature
Click for BNO085 product page
Winch servo requires smaller resistor to override radio output
configure PC12=!CHG as open drain, activate to turn on blue power button LED
holds relay coil off even if OPi is off
I2C address 0x48=72d but will not show up in this standalone config (see CV pin function)
I2C addr 52d =0x34
Fix JST headers to be actual size (too large now)
IMU BNO055 I2C addr 0x69
i2C addr 0x44=68 decimal
!ACOK Valid input supply indicator. Open-drain output. Pulled to low when the input voltage is greater than VIN_UVLO and below VIN_OVLO.
MAIN=battery after relay
Label on PCB to distinguish I2C bus!
!ACOK configure as PU - signals MPC2672 has power
Fixed 2.7kHz buzzer to signal boot and shutdown and SOS
band on cathode (-)
Add 10k pulldown to prevent buzzer on boot
Power buttons
R32: Solder for host controlled, do not solder for standalone Host-controlled does not work with OPi can be off. See https://forum.monolithicpower.com/t/mp2672-i2c-comms-with-power-disconnected/1952/11
heartbeat, PH4 mirrors OPi before Argo takes over for power button green LED

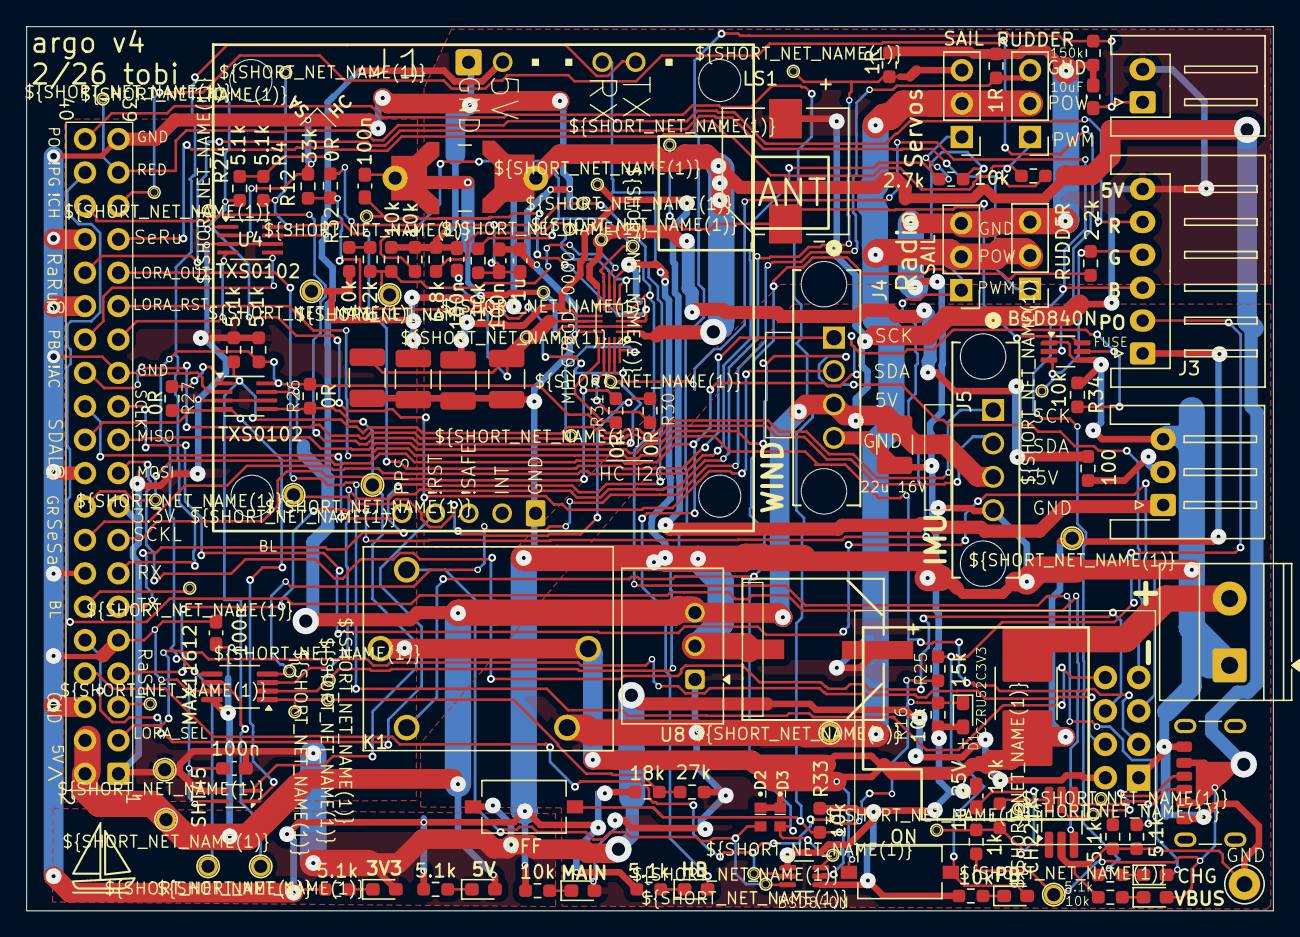
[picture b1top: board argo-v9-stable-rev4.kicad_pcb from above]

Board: 2 copper layers, 94.8 x 67.2 mm, 137 parts (0 on the bottom side), 73 nets.

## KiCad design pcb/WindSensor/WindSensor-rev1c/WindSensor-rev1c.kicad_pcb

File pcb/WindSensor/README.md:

# Argo Wind Sensor - Revision 1

## Overview

This is the Argo Wind Sensor PCB and 3D printed case design, including the boat hull housing cable gland entry and the replacement mast base part that increases the mast clearance over the deck to allow room for the cable gland. The wind sensor is designed to measure wind speed and direction for the Argo sailboat. 

It is based on Sensiorion reference design (since removed from sensorion because the page could not be migrated). Sensirion kindly supplied the step file as a starting point for the current design. The current design is combined with a mast mounting part that clamps to the mast backstay carbon fiber part.

The PCB design includes 3 SDP32 differential pressure sensors and 
an RGBW LED controller with RGBW LED. Sensors and LED controller are on the Argo I2C bus and are connected to Argo's computer via the 4-wire cable through the Molex SL-series SMD header. The mast mount part includes a set screw to provide strain relief for the SMD Molex header.

The PCB was designed in Kicad 9. The housing was designed in FreeCAD 1.1rc2.

The PCB was fabricated by JLCPCB.

See the argo ROS2 nodes anem.py and mastled.py for sensing and control of the wind sensor.

## Images

These images show a sample of the wind sensor housing and its design. The right image shows the air pipes from Sensirion SDP32 differential pressure sensors to the air pitot openings. 

<table>
  <tr>
    <td align="center">
      <b>Wind Sensor Housing Photo</b><br/>
      
    </td>
    <td align="center">
      <b>3D Turntable GIF</b><br/>
      
    </td>
    <td align="center">
      <b>Air Passages</b><br/>
      
    </td>
  </tr>
</table>

### Additional parts
<table>
  <tr>
    <td align="center">
      <b>Mast Step Up (1cm)</b><br/>
      
    </td>
    <td align="center">
      <b>Cable Gland Housing</b><br/>
      
    </td>
  </tr>
</table>

#### Hull entry cable gland
The 3D design of the cable gland hull entry through DF65 battery charger opening is part of the 3D FreeCAD design of the WindSensor.
- **Cabling**: I2C cable, Digikey Part: [839-30-00099-DS-ND](https://www.digikey.ch/en/products/detail/tensility-international-corp/30-00099/24671435)
  - **Description**: CBL 4CON 28AWG SHLD WHT 1M  
    - 4-conductor (1 pair twisted), Multi-Conductor Cable, White, 28 AWG  
    - Shielded (Foil, Braid)  
    - Length: 1.00m (3.28')  
    - Outer Diameter: 3.6mm  
    - 4 (1 Pair Twisted) Conductor Multi-Conductor Cable White 28 AWG Foil
  - **Datasheet**: [30-00099 (PDF)](https://tensility.s3.us-west-2.amazonaws.com/imports/product_spec_sheets/30-00099.pdf)
  - **Supplier**: digikey.ch  
  - **Approx. Price**: 2.62 CHF/m
- **Cable Gland**: Waterproofing cable guard for I2C cable entry  
  - **Part Number:** 281-3860-ND  
  - **Manufacturer:** Weidmüller (2583400000)  
  - **Supplier:** [Digi-Key](https://www.digikey.ch/products/de?keywords=281-3860)  
  - **Description:** Water-resistant cable entry for wind sensor I2C connection  
  - **Type:** Square Frame Grommet, Split  
    - Frame Size: 0.815" (20.70mm)  
    - Cable Range: 0.118" ~ 0.157" (3.00mm ~ 4.00mm)  
    - Color: Gray  
  - **Price:** ~3.70 CHF (digikey.ch)

#### Mast step up
The mast is raised by 1cm to allow clearance of the main sail boom over the cable gland housing. The 3D design of this replacement for the standard DF65 mast base plate is part of the WindSensor 3D design in FreeCAD.

## PCB and specifications

### PCB Views

<div align="center">
  <b>WindSensor PCB 3D View (PCB dims 20x20mm)</b><br/>
  
</div>

<div align="center">
  <b>WindSensor PCB Schematic</b><br/>
  
</div>

<div align="center">
  <b>WindSensor PCB Layout(PCB dims 20x20mm)</b><br/>
  
</div>

<div align="center">
  <b>WindSensor PCB Layout(PCB dims 20x20mm)</b><br/>
  
</div>

Sensors are numbered left to right on the PCB. On every SDP32, the **upper** (windward) port is wired to the **negative** (−) pressure port; I2C reports P(+) − P(−), so headwind on the center tube gives **negative** raw readings. The ±120° pitot paths invert sign relative to the center sensor. `anem.py` negates CTR only; CW/CCW keep raw sign.

| Label | I2C address | Angle (looking down on mast) | `anem.py` sign (after offset subtract) |
|-------|-------------|----------------------------|----------------------------------------|
| CW    | 0x21        | +120° (clockwise from bow) | × +1 (routing inverted vs CTR)         |
| CTR   | 0x22        | 0° (bow/stern)             | × −1 (negate I2C; − port on upper)     |
| CCW   | 0x23        | −120° / 240° CCW from bow  | × +1 (routing inverted vs CTR)         |

### Electrical
- **Supply Voltage**: 5V
- **Operating Current**: About 160mA max (3 LEDS, each max 50mA)
- **Communication Interface**: I2C

### Physical
- **Board Dimensions**: 20x20mm
- **Number of Layers**: 2
- **Surface Finish**: ENIG
- **Connector**: Molex SL series SMD. Strain relief to wind sensor housing base mast mounting part via posts and M3 set screw.

## Design Files

This directory contains:
- Schematic files (`.kicad_sch` Kicad Version 9)
- PCB layout files (`.kicad_pcb` ) 
- 3D models (if applicable)

## Bill of Materials (BOM)

The BOM is generated from Kicad
Parts include datasheet links and Digikey or Farnell part links.

## Manufacturing

### Gerber Files
Gerber files are generated from kicad in the `gerbers/` directory. These can be sent directly to a PCB manufacturer.

### Fabrication Notes
- Minimum trace width: 0.2mm
- Minimum via size: 0.3mm

## Known Issues

- None currently documented for Rev 1

## Revision History

### Rev 1 (Initial Release)
- 2nd version of PCB
- Date: Feb 2026

### Rev 0 
- Initial design done by ETH semester student Andrea Mock
- Date: ca. 2019
- Based on Sensirion reference design, no longer available

## Contact

For questions or issues related to this PCB design, please contact Tobi Delbruck.

## Credits
Thanks to Sensirion (Alex Roos and colleagues) for making the original Sensirion prototype step file avaialable again to enable rev 1.
## License

Same as argo project.

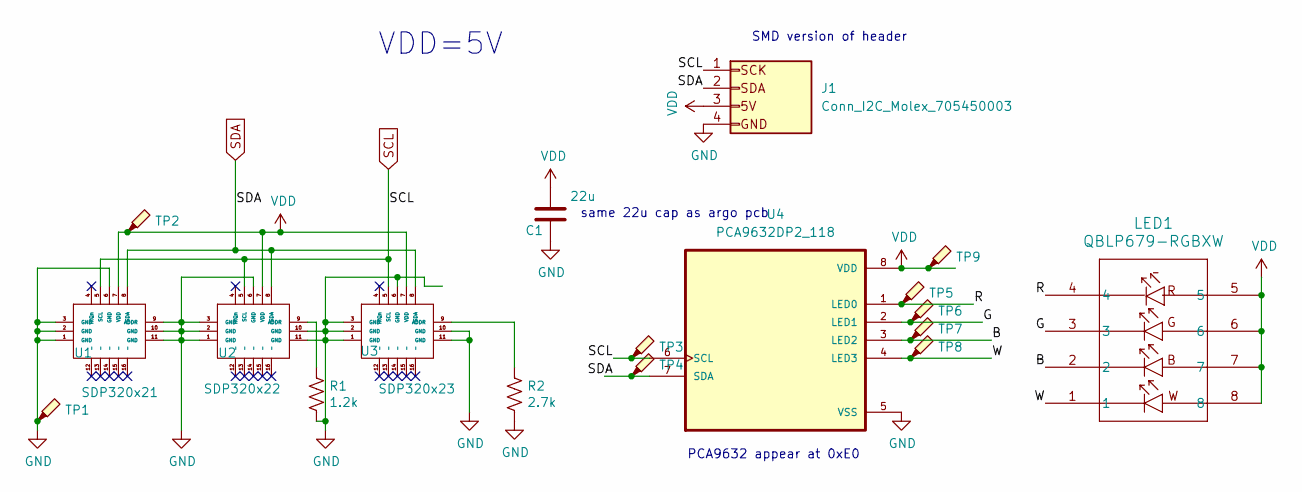
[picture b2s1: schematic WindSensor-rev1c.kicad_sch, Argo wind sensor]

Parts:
C1: 22u; C_1210_3225Metric_Pad1.33x2.70mm_HandSolder
J1: Conn_I2C_Molex_705450003; CONN_SD-74099-1000_04_MOL
LED1: QBLP679-RGBXW; LED_QBLP679E-RGBW
R1: 1.2k; R_0603_1608Metric_Pad0.98x0.95mm_HandSolder
R2: 2.7k; R_0603_1608Metric_Pad0.98x0.95mm_HandSolder
TP1, TP2, TP3, TP4: TestPoint_Probe_autonamed; TestPoint_scope_probe_autonamed
TP5, TP6, TP7, TP8, TP9: TestPoint_Probe_autonamed; TestPoint_scope_small_autonamed
U1: SDP320x21; SDP32
U2: SDP320x22; SDP32
U3: SDP320x23; SDP32
U4: PCA9632DP2_118; SOP65P490X110-8N; PARTREV 5

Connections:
/B: LED1.2, TP7.1, U4.3 (LED2)
/G: LED1.3, TP6.1, U4.2 (LED1)
/R: LED1.4, TP5.1, U4.1 (LED0)
/W: LED1.1, TP8.1, U4.4 (LED3)
GND: C1.1, J1.4 (GND), R1.2, R2.2, TP1.1, U1.1 (GND), U1.2 (GND), U1.3 (GND), U1.6 (GND), U1.9 (ADDR), U1.10 (GND), U1.11 (GND), U1.17 (GND), U1.18 (GND), U2.1 (GND), U2.2 (GND), U2.3 (GND), U2.6 (GND), U2.10 (GND), U2.11 (GND), U2.17 (GND), U2.18 (GND), U3.1 (GND), U3.2 (GND), U3.3 (GND), U3.6 (GND), U3.10 (GND), U3.11 (GND), U3.17 (GND), U3.18 (GND), U4.5 (VSS)
unnamed: R1.1, U2.9 (ADDR)
unnamed: R2.1, U3.9 (ADDR)
SCL: J1.1 (SCLK), TP3.1, U1.5 (SCL), U2.5 (SCL), U3.5 (SCL), U4.6 (SCL)
SDA: J1.2 (SDA), TP4.1, U1.8 (SDA), U2.8 (SDA), U3.8 (SDA), U4.7 (SDA)
VDD: C1.2, J1.3 (5V), LED1.5, LED1.6, LED1.7, LED1.8, TP2.1, TP9.1, U1.7 (VDD), U2.7 (VDD), U3.7 (VDD), U4.8 (VDD)

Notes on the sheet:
VDD=5V
same 22u cap as argo pcb
PCA9632 appear at 0xE0
SMD version of header

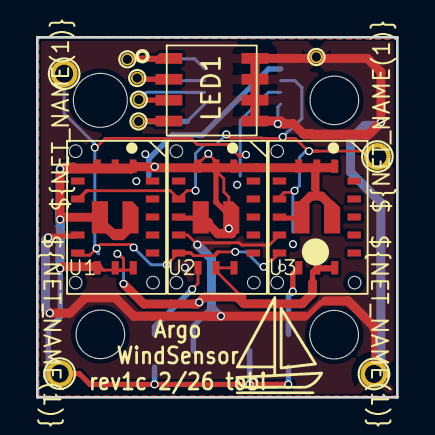
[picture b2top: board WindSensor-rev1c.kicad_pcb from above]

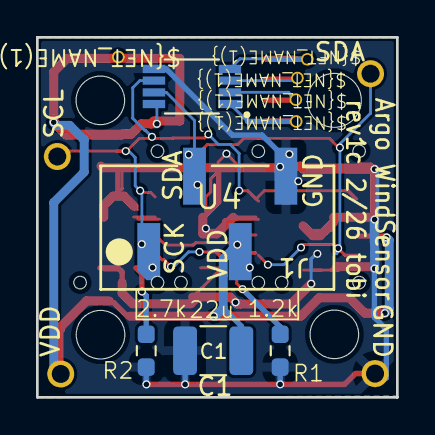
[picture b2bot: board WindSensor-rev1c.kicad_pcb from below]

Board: 2 copper layers, 20.0 x 20.0 mm, 22 parts (5 on the bottom side), 10 nets.

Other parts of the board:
H1, H2, H3, H4: (no value)

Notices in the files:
README.md:
License:
BSD License - See package.xml for details
pcb/sparkfun/SparkFun_IMU_Breakout_ICM-20948/SparkFun_IMU_Breakout_ICM-20948.kicad_sch:
Released under the Creative Commons
https://creativecommons.org/licenses/by-sa/4.0
parts and their libraries:
Released under the Creative Commons Attribution Share-Alike 4.0 License
